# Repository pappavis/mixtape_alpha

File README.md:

# Wat is Mixtape Alpha?
MixTape Alpga is 'n Atmel328P (Arduino) gebasseerd aanraakgevoelig synth.  Die projekbestande omvat schema bestand vir EagleCAD en diebronkode om dit te laat werk. <br/><br/>

<br/>

## Gebruiksinstruksies:<br/>
1. Download EagleCAD<br/>
2. Laai die Schema bestand in Eagle en bekyk dit.<br/>
<br/>

## Printplaat laat maak?<br/>
Om self printplate te laat maak, upload die GERBERs mixtape2_gerber.zip na 'n diens soos http://JLCPCB.com of http://dirtypcbs.com<br/>
<br/>

<br/>
<br/>

# CREDITS:
Die oorspronklike Mixtape project uit 2013 van MIT Music Lab is op http://wiki.openmusiclabs.com/wiki/MixtapeAlpha<br/>
Ook was daar 'n crowdfunding projek op https://www.crowdsupply.com/open-music-labs/mixtape-alpha <br/>
Ek het dit vir gemak op Github geplaas.<br/>
<br/>

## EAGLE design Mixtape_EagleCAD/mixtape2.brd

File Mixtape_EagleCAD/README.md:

## Wat is dit
Dit is die bronbestanden vir EagleCAD en gerbers om by http://jlcpcb.com te laat maak.

## Schema
<br/>
<br/>
## Printplaat boven
 <br/>
<br/>

## Printplaat onder

<br>

## Dokumentasie
sien wiki op http://wiki.openmusiclabs.com/wiki/MixtapeAlpha <br/>
en algemeen info op http://www.openmusiclabs.com/projects/mixtape_alpha/ <br/>

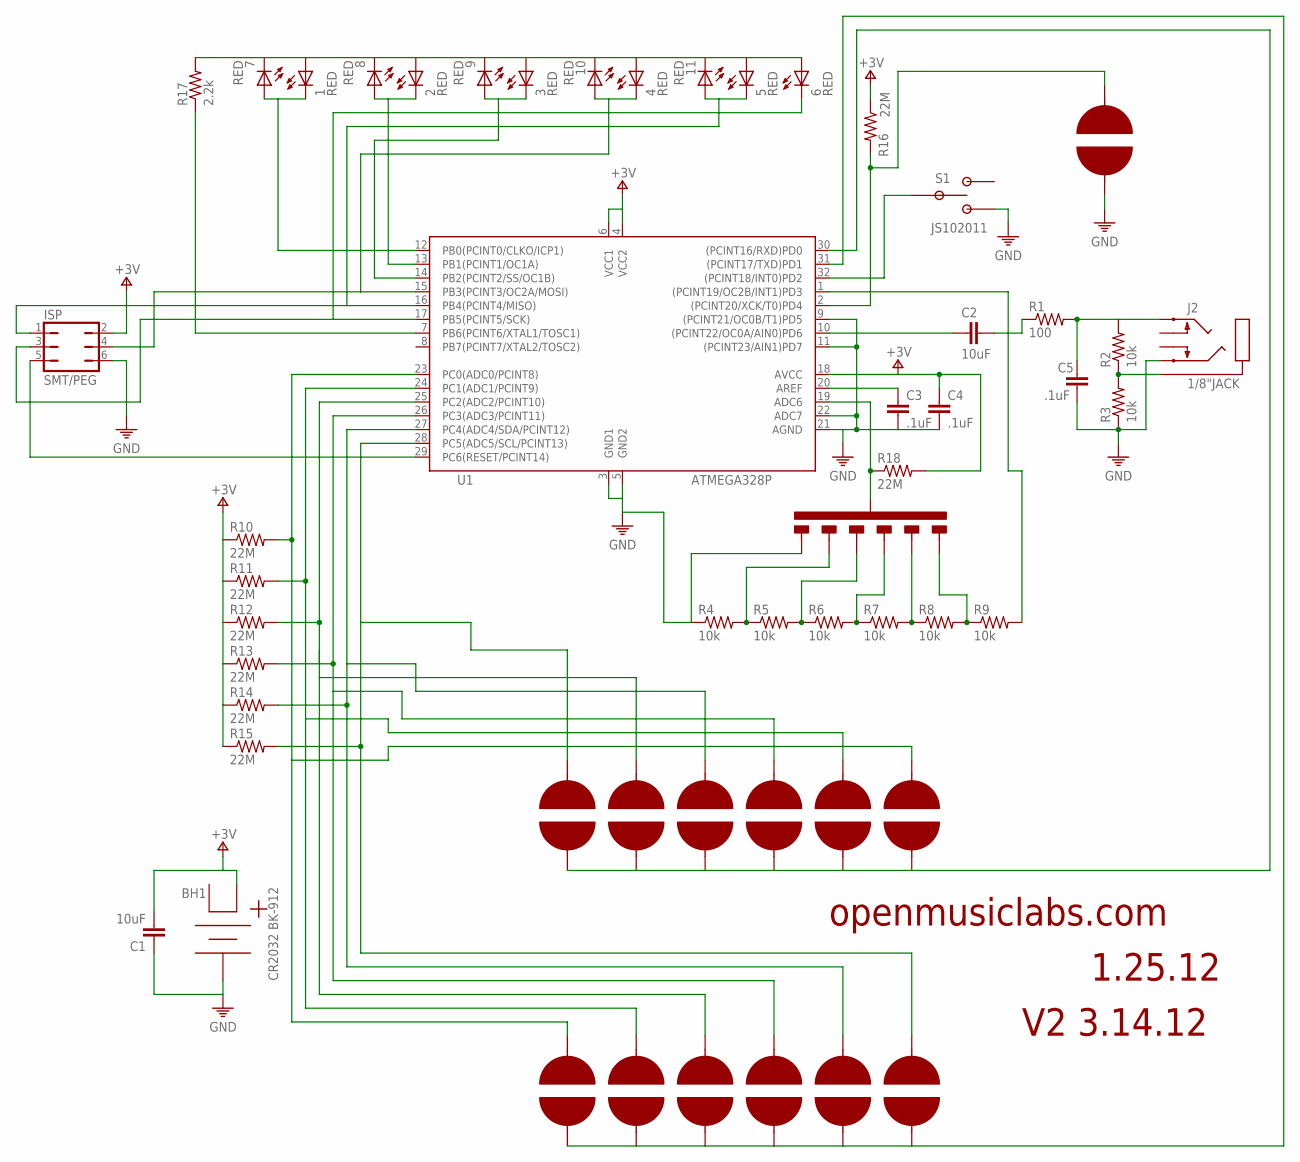
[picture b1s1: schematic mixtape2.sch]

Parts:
1, 2, 3, 4, 5, 6, 7, 8, 9, 10, 11: RED; LED-SMT-91-21
BH1: CR2032 BK-912; BAT-HOLD-BK-912
C1, C2: 10uF; 0805/SMALL
C3, C4, C5: .1uF; 0603-SM
ISP: SMT/PEG; JMP/6P/DIP/SMT/PEG
J2: 1/8"JACK; 1/8"JACK/STEREO/SMT
R1: 100; 0603-SM
R2, R3, R4, R5, R6, R7, R8, R9: 10k; 0603-SM
R10, R11, R12, R13, R14, R15, R16, R18: 22M; 0603-SM
R17: 2.2k; 0603-SM
S1: JS102011; SWITCH/SLIDE/JS102011
U1: ATMEGA328P; 32-TQFP-NOMOD
U$1: PAD/TOUCH/WHEEL
U$2, U$3, U$4, U$5, U$6, U$7, U$8: PAD/TOUCH; PAD/TOUCH/DOT
U$9: PAD/TOUCH/SLIDERSLIDER; PAD/TOUCH/SLIDER

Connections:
unnamed: R17.P$1 (1), U1.7 (PB6(PCINT6/XTAL1/TOSC1))
unnamed: U1.31 ((PCINT17/TXD)PD1), U$2.P$2, U$3.P$2, U$4.P$2, U$5.P$2, U$6.P$2, U$7.P$2
unnamed: R13.P$2 (2), U1.26 (PC3(ADC3/PCINT11)), U$1.P$7, U$5.P$1
unnamed: U1.30 ((PCINT16/RXD)PD0), U$1.P$2, U$1.P$4, U$1.P$6, U$1.P$8, U$1.P$10, U$1.P$12
unnamed: ISP.5, U1.29 (PC6(RESET/PCINT14))
unnamed: J2.P$1 (1), R2.P$1 (1), R3.P$2 (2)
unnamed: C2.1, R1.P$1 (1)
unnamed: C5.P$1 (1), J2.P$5 (5), R1.P$2 (2), R2.P$2 (2)
unnamed: C2.2, U1.10 ((PCINT22/OC0A/AIN0)PD6)
unnamed: S1.P$2, U1.32 ((PCINT18/INT0)PD2)
unnamed: C3.P$1 (1), U1.20 (AREF)
unnamed: R4.P$2 (2), R5.P$1 (1), U$9.P$6
unnamed: R5.P$2 (2), R6.P$1 (1), U$9.P$5
unnamed: R6.P$2 (2), R7.P$1 (1), U$9.P$4
unnamed: R8.P$2 (2), R9.P$1 (1), U$9.P$2
unnamed: R9.P$2 (2), U1.1 ((PCINT19/OC2B/INT1)PD3)
unnamed: 1.P$1 (C), 7.P$2 (A), U1.12 (PB0(PCINT0/CLKO/ICP1))
unnamed: 2.P$1 (C), 8.P$2 (A), U1.13 (PB1(PCINT1/OC1A))
unnamed: 3.P$1 (C), 9.P$2 (A), U1.14 (PB2(PCINT2/SS/OC1B))
unnamed: 4.P$1 (C), 10.P$2 (A), ISP.4, U1.15 (PB3(PCINT3/OC2A/MOSI))
unnamed: 5.P$1 (C), 11.P$2 (A), ISP.1, U1.16 (PB4(PCINT4/MISO))
unnamed: 1.P$2 (A), 2.P$2 (A), 3.P$2 (A), 4.P$2 (A), 5.P$2 (A), 6.P$2 (A), 7.P$1 (C), 8.P$1 (C), 9.P$1 (C), 10.P$1 (C), 11.P$1 (C), R17.P$2 (2)
unnamed: R16.P$2 (2), U1.2 ((PCINT20/XCK/T0)PD4), U$8.P$1
unnamed: R12.P$2 (2), U1.25 (PC2(ADC2/PCINT10)), U$1.P$3, U$4.P$1
unnamed: R14.P$2 (2), U1.27 (PC4(ADC4/SDA/PCINT12)), U$1.P$5, U$6.P$1
unnamed: R15.P$2 (2), U1.28 (PC5(ADC5/SCL/PCINT13)), U$1.P$1, U$7.P$1
unnamed: R18.P$1 (1), U1.19 (ADC6), U$9.P$1
unnamed: 6.P$1 (C), ISP.3, U1.17 (PB5(PCINT5/SCK))
unnamed: R11.P$2 (2), U1.24 (PC1(ADC1/PCINT9)), U$1.P$9, U$3.P$1
unnamed: R10.P$2 (2), U1.23 (PC0(ADC0/PCINT8)), U$1.P$11, U$2.P$1
unnamed: R7.P$2 (2), R8.P$1 (1), U$9.P$3
PE: BH1.P$3, C1.1, C3.P$2 (2), C4.P$2 (2), C5.P$2 (2), ISP.6, J2.P$3 (2), R3.P$1 (1), R4.P$1 (1), S1.P$1, U1.3 (GND1), U1.5 (GND2), U1.9 ((PCINT21/OC0B/T1)PD5), U1.11 ((PCINT23/AIN1)PD7), U1.21 (AGND), U1.22 (ADC7), U$8.P$2, U$9.P$7
V+: BH1.P$1, C1.2, C4.P$1 (1), ISP.2, R10.P$1 (1), R11.P$1 (1), R12.P$1 (1), R13.P$1 (1), R14.P$1 (1), R15.P$1 (1), R16.P$1 (1), R18.P$2 (2), U1.4 (VCC2), U1.6 (VCC1), U1.18 (AVCC)

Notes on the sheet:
openmusiclabs.com
1.25.12
V2 3.14.12

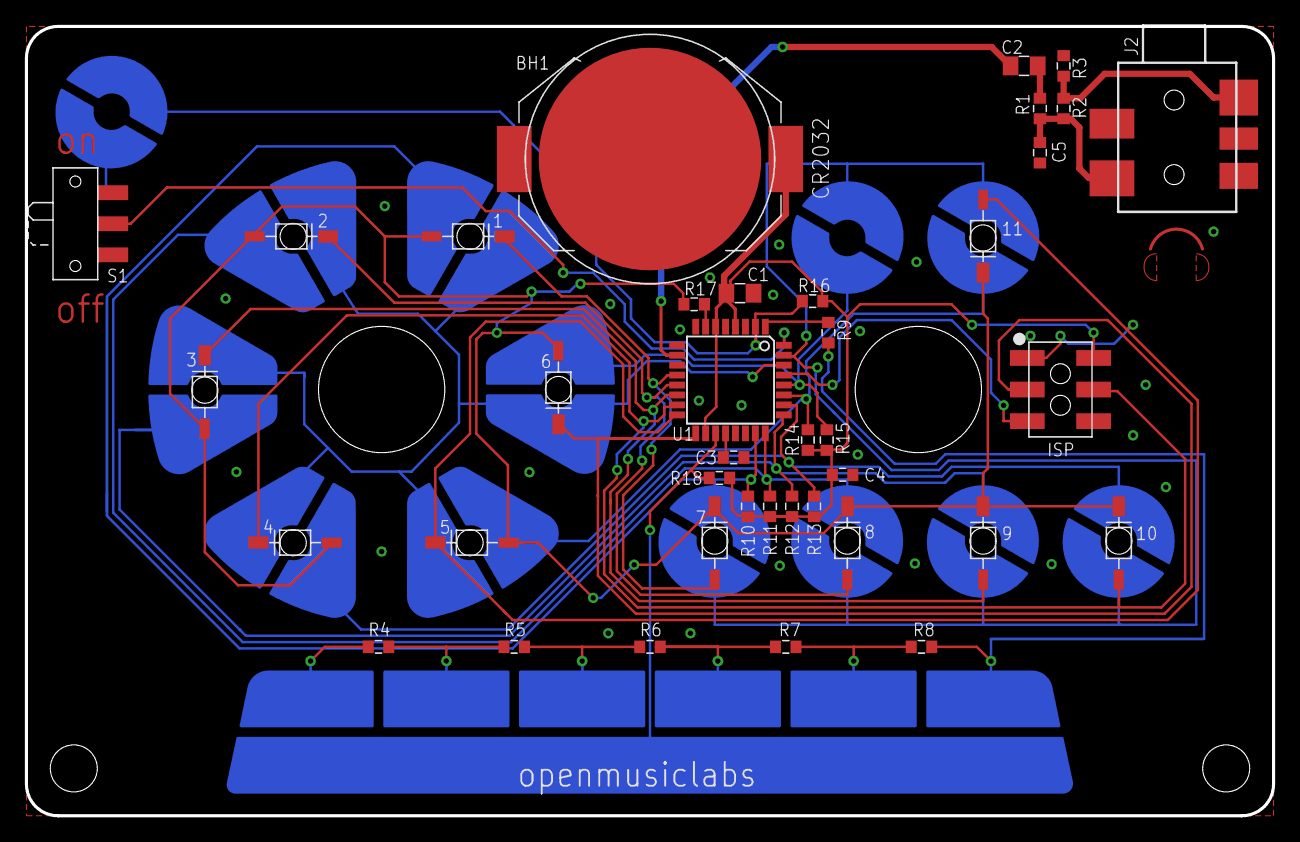
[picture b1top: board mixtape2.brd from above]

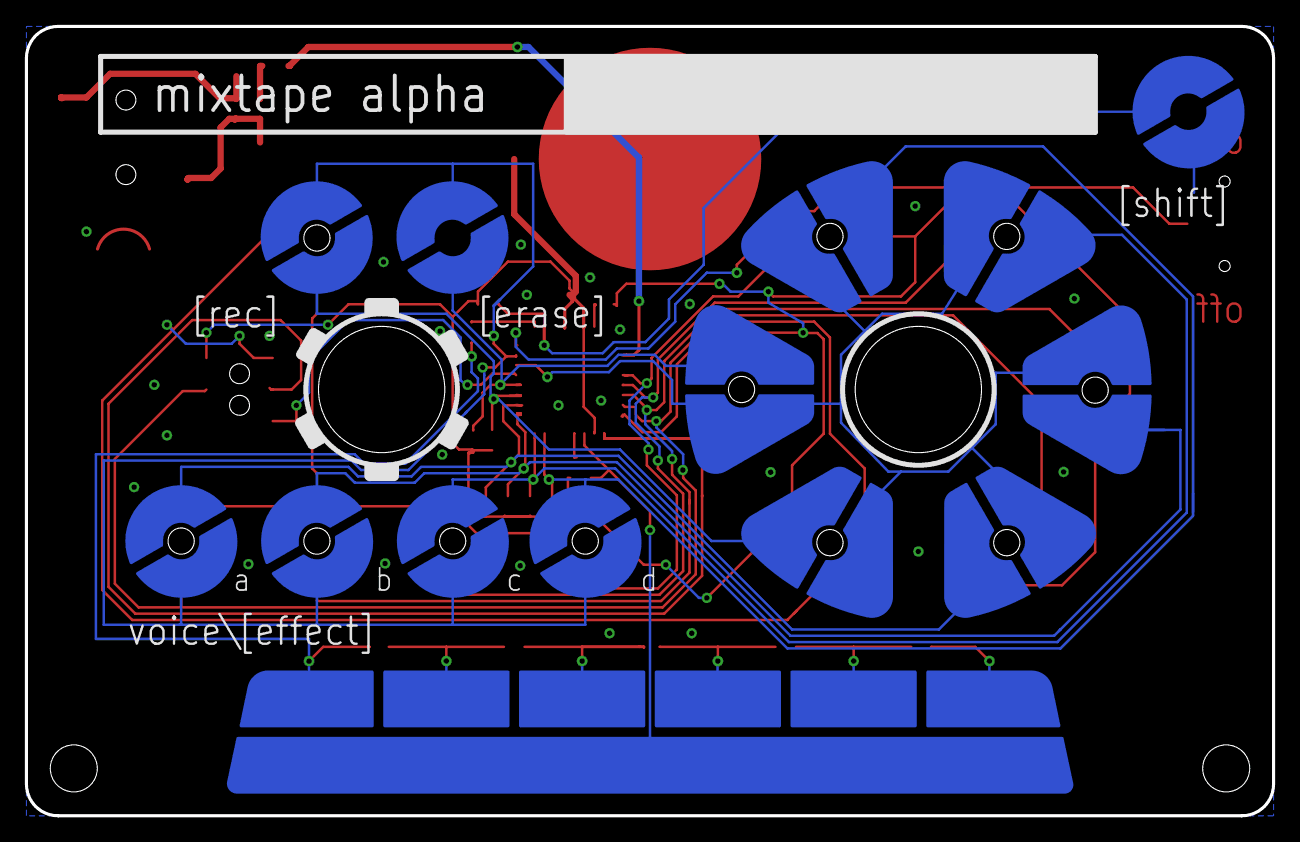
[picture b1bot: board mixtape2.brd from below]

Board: 2 copper layers, 100.3 x 63.5 mm, 48 parts (9 on the bottom side), 33 nets.

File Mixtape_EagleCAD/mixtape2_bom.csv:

DESIGNATOR,PART,VALUE,PACKAGE,DETAILS,PART #
,,,,,
1,LED,RED,SMT/REVERSE,"25 degree, 482mCd","EVERLIGHT, 91-21SURC/S530-A2/TR10"
2,LED,RED,SMT/REVERSE,"25 degree, 482mCd","EVERLIGHT, 91-21SURC/S530-A2/TR10"
3,LED,RED,SMT/REVERSE,"25 degree, 482mCd","EVERLIGHT, 91-21SURC/S530-A2/TR10"
4,LED,RED,SMT/REVERSE,"25 degree, 482mCd","EVERLIGHT, 91-21SURC/S530-A2/TR10"
5,LED,RED,SMT/REVERSE,"25 degree, 482mCd","EVERLIGHT, 91-21SURC/S530-A2/TR10"
6,LED,RED,SMT/REVERSE,"25 degree, 482mCd","EVERLIGHT, 91-21SURC/S530-A2/TR10"
7,LED,RED,SMT/REVERSE,"25 degree, 482mCd","EVERLIGHT, 91-21SURC/S530-A2/TR10"
8,LED,RED,SMT/REVERSE,"25 degree, 482mCd","EVERLIGHT, 91-21SURC/S530-A2/TR10"
9,LED,RED,SMT/REVERSE,"25 degree, 482mCd","EVERLIGHT, 91-21SURC/S530-A2/TR10"
10,LED,RED,SMT/REVERSE,"25 degree, 482mCd","EVERLIGHT, 91-21SURC/S530-A2/TR10"
11,LED,RED,SMT/REVERSE,"25 degree, 482mCd","EVERLIGHT, 91-21SURC/S530-A2/TR10"
,,,,,
U1,uC,Atmega328P-AU,32TQFP,,
,,,,,
C1,capacitor,10uF,0805,CERAMIC,
C2,capacitor,10uF,0805,CERAMIC,
C3,capacitor,0.1uF,0603,CERAMIC,
C4,capacitor,0.1uF,0603,CERAMIC,
C5,capacitor,0.1uF,0603,CERAMIC,
,,,,,
R1,resistor,100ohm,0603,,
R2,resistor,10k,0603,,
R3,resistor,10k,0603,,
R4,resistor,10k,0603,,
R5,resistor,10k,0603,,
R6,resistor,10k,0603,,
R7,resistor,10k,0603,,
R8,resistor,10k,0603,,
R9,resistor,10k,0603,,
R10,resistor,22M,0603,,
R11,resistor,22M,0603,,
R12,resistor,22M,0603,,
R13,resistor,22M,0603,,
R14,resistor,22M,0603,,
R15,resistor,22M,0603,,
R16,resistor,22M,0603,,
R17,resistor,2.2k,0603,,
R18,resistor,22M,0603,,
,,,,,
S1,switch,slide,SMT,,"C&K, JS102011SAQN"
J2,1/8 jack,stereo/switched,SMT,,Kobiconn 161-2805-E or CUI SJ1-3515-SMT
BH1,battery holder,CR2032,SMT,,"MEMORY PROTECTION DEVICES, BK-912"

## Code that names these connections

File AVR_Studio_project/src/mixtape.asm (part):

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
; pin usage
;
; pb0:5 = led1:6, led7:11
; pb6   = led direction, 1 = led1:6, 0 = led7:11
; pb7   = nc
; pc0:5 = pad1:6, pad7:12
; pc6   = reset
; pd0   = pad1:6 control, 0 = active, 1 = off
; pd1   = pad7:12 control, 0 = active, 1 = off
; pd2   = power switch, 0 = on, 1 = off, int0
; pd3   = slider control, 1 = on, 0 = off
; pd4   = shift pad
; pd5,7 = shorted to ground, always set to input, pullups off
; pd6   = pwm out, oc0a, t0
; adc6  = slider analog input
; adc7  = nc
; aref  = cap, internal vcc
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out portc,r16 ; turn off pullups for portc, except reset pin
ldi r16,$00
out ddrc,r16 ; set all of portc to input
ldi r16,(0<<pd7)|(0<<pd6)|(0<<pd5)|(1<<pd4)|(1<<pd3)|(1<<pd2)|(1<<pd1)|(1<<pd0)
out portd,r16 ; pullups on for pd2,4 high for pd0,1,4, low for all else
ldi r16,$4b
out ddrd,r16 ; pd0,1,3,6 output, rest input

;setup power reduction registers
ldi r16,$86
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sbrs r30,$05 ; check for overflow
rjmp interrupt_wait ; keep checking
;set to read pad1:6
ldi r17,(0<<pd7)|(0<<pd6)|(0<<pd5)|(0<<pd4)|(1<<pd3)|(1<<pd2)|(1<<pd1)|(0<<pd0)
sbis portd,$00 ; check which pads were being scanned
;set to read pad7:12
ldi r17,(0<<pd7)|(0<<pd6)|(0<<pd5)|(0<<pd4)|(1<<pd3)|(1<<pd2)|(0<<pd1)|(1<<pd0)
out portd,r17 ; switch to other set of pads
clr r25 ; prep register for storing button result

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out portb,r16 ; turn off leds
ldi r16,$7f
out portc,r16 ; turn on pullups for all portc
ldi r16,(0<<pd7)|(0<<pd6)|(0<<pd5)|(1<<pd4)|(0<<pd3)|(1<<pd2)|(1<<pd1)|(1<<pd0)
out portd,r16 ; shut off pad controls and turn on pullup for shift button

;go to sleep
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
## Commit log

2018-10-23 Eerste toevoeging 20181023
2018-11-12 Eagle BRD toegevoegd
2018-12-04 Bygewerkt na EagleCAD 9 formaat
2018-12-04 KiCAD 5.0-versie
2019-09-11 Eerste commit
    Bill of materials
2019-09-11 Pick n place bestande toegevoegd.
